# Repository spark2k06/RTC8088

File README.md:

# RTC8088
Real Time Clock for your PC XT. Very low profile, simple and open hardware.

## Hardware Documentation

### Schematic and PCB Layout

[Schematic - Version 3.0](KiCad/RTC8088-Schematic-3.0.pdf)

[PCB Layout - Version 3.0](KiCad/RTC8088-Board-3.0.pdf)

### Swiches and Jumpers

#### SW1 - RTC I/O address select

I/O Address  | SW1.1 | SW 1.2 | SW 1.3
------------ | ----- | ------ | ------
0x70         | OFF   | OFF    | OFF
0x240        | ON    | OFF    | OFF
0x2A0        | OFF   | ON     | OFF
0x2C0        | ON    | ON     | OFF
0x340        | OFF   | OFF    | ON
0x3A0        | ON    | OFF    | ON
0x3C0        | OFF   | ON     | ON
Reserved     | ON    | ON     | ON

* Note 1: The table above gives the addresses in the supplied SPLD fuse map. The selection can be changed by reprogramming the SPLD
* Note 2: "Reserved" address is set to 0x70 in the supplied SPLD fuse map. It is recommended to use this setting when adding a custom I/O address to the SPLD

#### JP1 - Clear CMOS

Position       | Description
-------------- | -----------------
open (default) | Normal operation
closed         | Clear NVRAM memory

### Bill of Materials

#### Version 3.0

[RTC8088 project on Mouser.com](https://www.mouser.com/ProjectManager/ProjectDetail.aspx?AccessID=2877d21cfa) - View and order all components except of the FDC and the PCB.

[RTC8088 on OSH Park](https://oshpark.com/shared_projects/bAF8uwKL) - View and order the PCB.

Component type     | Reference | Description                                     | Quantity | Possible sources and notes 
------------------ | --------- | ----------------------------------------------- | -------- | --------------------------
PCB                |           | RTC8088 PCB - Version 3.0                       | 1        | Order from your favorite PCB manufacturer using provided Gerber files
Integrated Circuit | U1        | DS12885+ - RTC, 24 pin DIP                      | 1        | Mouser [700-DS12885](https://www.mouser.com/ProductDetail/700-DS12885) or [700-DS12885N](https://www.mouser.com/ProductDetail/700-DS12885N)
Integrated Circuit | U2        | ATF16V8B-15PU - Simple Programmable Logic Device, 20 pin DIP | 1 | Mouser [556-AF16V8B15PU](https://www.mouser.com/ProductDetail/556-AF16V8B15PU) or GAL16V8
Quartz Crystal     | Y1        | 32768 Hz, 6 pF                                  | 1        | Mouser [815-AB26T32768KHZ6B](https://www.mouser.com/ProductDetail/815-AB26T32768KHZ6B), [520-ECS327-6-13-X](https://www.mouser.com/ProductDetail/520-ECS327-6-13-X), or [628-VT200F-6PF20PPM](https://www.mouser.com/ProductDetail/628-VT200F-6PF20PPM)
Battery Holder     | BT1       | CR2032 battery holder                           | 1        | Mouser [122-2620-GR](https://www.mouser.com/ProductDetail/122-2620-GR) or [122-2420-GR](https://www.mouser.com/ProductDetail/122-2420-GR)
Battery            | BT1       | CR2032 battery                                  | 1        | Mouser [81-CR2032](https://www.mouser.com/ProductDetail/81-CR2032), [658-CR2032](https://www.mouser.com/ProductDetail/658-CR2032), or [614-CR2032-200](https://www.mouser.com/ProductDetail/614-CR2032-200)
Capacitor          | C1        | 0.1 uF, 50V, MLCC, 5 mm pitch                   | 1        | Mouser [594-K104K15X7RF53H5](https://www.mouser.com/ProductDetail/594-K104K15X7RF53H5) or [810-FG28X7R1H104KNT6](https://www.mouser.com/ProductDetail/810-FG28X7R1H104KNT6)
Resistor Array     | RN1       | 10 kohm, bussed, 5 pin SIP                      | 1        | Mouser [652-4605X-1LF-10K](https://www.mouser.com/ProductDetail/652-4605X-1LF-10K) or [652-4605X-AP1-103LF](https://www.mouser.com/ProductDetail/652-4605X-AP1-103LF)
DIP Switch         | SW1       | DIP switch, 3 position, SPST                    | 1        | Mouser [774-2103MS](https://www.mouser.com/ProductDetail/774-2103MS)
Pin Header         | JP1       | 2 pin header, 2.54 mm pitch                     | 1        | Mouser [649-68002-102HLF](https://www.mouser.com/ProductDetail/649-68002-102HLF)
Jumper             | JP1       | Shunt, 2 pin, 2.54 mm pitch                     | 1        | Mouser [806-SX1100-B](https://www.mouser.com/ProductDetail/806-SX1100-B)
IC Socket          | U1        | 20 pin DIP, 2.54 mm pitch, 7.62 mm row spacing  | 1        | Mouser [649-DILB20P-223TLF](https://www.mouser.com/ProductDetail/649-DILB20P-223TLF)
IC Socket          | U2        | 24 pin DIP, 2.54 mm pitch, 15.24 mm row spacing | 1        | Mouser [649-DILB24P-223TLF](https://www.mouser.com/ProductDetail/649-DILB24P-223TLF)

## Software

The board is supported by the [8088 BIOS](https://github.com/skiselev/8088_bios) and [GLaTICK BIOS Extension](https://github.com/640-KB/GLaTICK).

## Release Notes

### Changes

* Version 3.0
  * Add I/O address configuration switches
  * Remove IRQ configuration jumpers and IRQ support
* Version 2.0
  * Aitor RTC8088
* Version 1.0
  * Initial version

### Known Issues

* No known issues

### Wishlist

* None so far

## Red Tape

### Licensing

RTC8088 is an open source hardware project. The hardware design itself, including schematic and PCB layout design files are licensed under the strongly-reciprocal variant of [CERN Open Hardware Licence version 2](license-cern_ohl_s_v2.txt). The SPLD code is licensed under [GNU General Public License v3](license-gpl-3.0.txt). Documentation, including this file, is licensed under the [Creative Commons Attribution-ShareAlike 4.0 International License](license-cc-by-sa-4.0.txt).

## More information

### Orignal RTC8088 Project Description
https://hackaday.io/project/168972-rtc-isa-8-bits-pcxt

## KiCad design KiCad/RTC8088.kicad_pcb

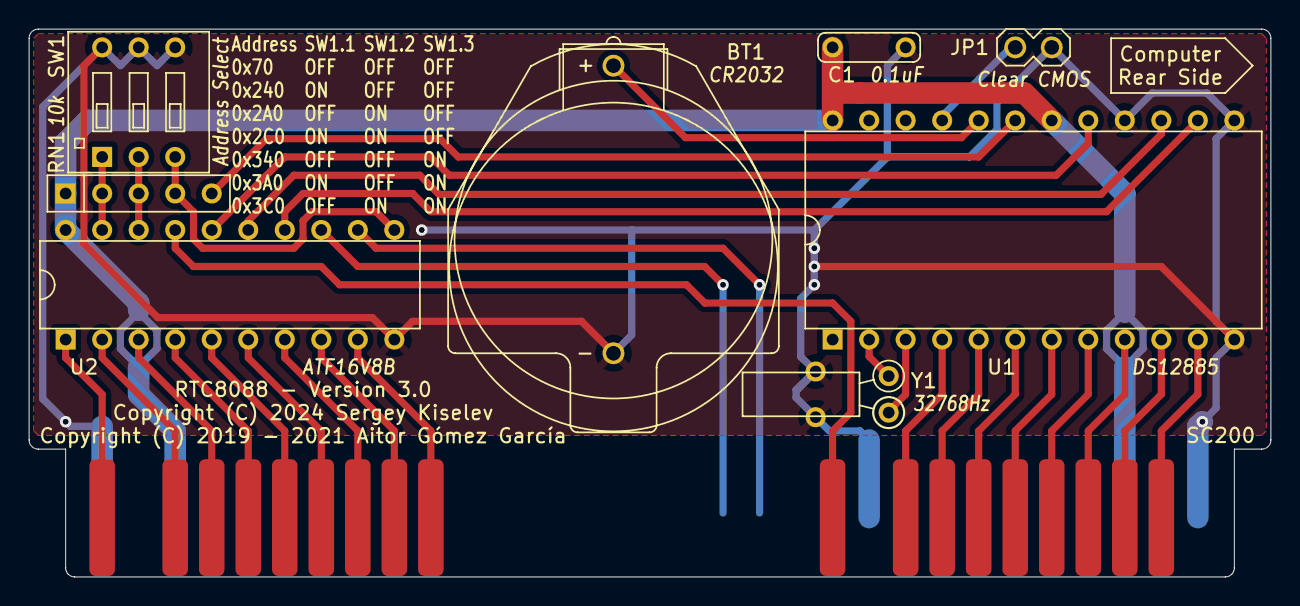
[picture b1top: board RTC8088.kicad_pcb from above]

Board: 2 copper layers, 86.4 x 38.1 mm, 9 parts (0 on the bottom side), 33 nets.

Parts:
BT1: CR2032; Battery_Holder_CR2032_Universal
BUS1: BUSPC_DEV; Conn_Edge_PCB_ISA8
C1: 0.1uF; Cap_Cer_508
JP1: Clear CMOS; Conn_Pin_Header_2x1_2.54mm_NoKey
RN1: 10k; Conn_SIL5
SW1: Address Select; Switch_DIP_3_Positions
U1: DS12885; IC_DIP24_600
U2: ATF16V8B; IC_DIP20_300
Y1: 32768Hz; Crystal_32K_Horiz

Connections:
/A0: BUS1.62 (SA0), U2.1 (I/CLK)
/A2: BUS1.60 (SA2), U2.2 (I1)
/A3: BUS1.59 (SA3), U2.3 (I2)
/A4: BUS1.58 (SA4), U2.4 (I3)
/A5: BUS1.57 (SA5), U2.5 (I4)
/A6: BUS1.56 (SA6), U2.6 (I5)
/A7: BUS1.55 (SA7), U2.7 (I6)
/A8: BUS1.54 (SA8), U2.8 (I7)
/A9: BUS1.53 (SA9), U2.9 (I8)
/AEN: BUS1.42 (AEN), U2.17 (I/O3)
/AS0: RN1.2 (R1), SW1.1, U2.19 (I/O1)
/AS1: RN1.3 (R2), SW1.2, U2.18 (I/O2)
/AS2: RN1.4 (R3), SW1.3, U2.11 (I9/~OE)
/D0: BUS1.40 (SD0), U1.4 (AD0)
/D1: BUS1.39 (SD1), U1.5 (AD1)
/D2: BUS1.38 (SD2), U1.6 (AD2)
/D3: BUS1.37 (SD3), U1.7 (AD3)
/D4: BUS1.36 (SD4), U1.8 (AD4)
/D5: BUS1.35 (SD5), U1.9 (AD5)
/D6: BUS1.34 (SD6), U1.10 (AD6)
/D7: BUS1.33 (SD7), U1.11 (AD7)
/IOR: BUS1.14 (IOR), U2.13 (I/O7)
/IOW: BUS1.13 (IOW), U2.12 (I/O8)
/RTCALE: U1.14 (AS), U2.14 (I/O6)
/RTCRD: U1.17 (DS), U2.16 (I/O4)
/RTCWR: U1.15 (R/~W), U2.15 (I/O5)
/~IRQ: RN1.5 (R4), U1.19 (~IRQ)
GND: BT1.2 (-), BUS1.1 (GND), BUS1.10 (GND), BUS1.31 (GND), C1.2, JP1.2 (B), SW1.4, SW1.5, SW1.6, U1.12 (GND), U1.13 (~CS), U1.16 (GND), U2.10 (GND), Y1.3
unnamed: BT1.1 (+), U1.20 (VBAT)
unnamed: JP1.1 (A), U1.21 (~RCLR)
unnamed: U1.2 (X1), Y1.1
unnamed: U1.3 (X2), Y1.2
VCC: BUS1.3 (VCC), BUS1.29 (VCC), C1.1, RN1.1 (common), U1.18 (~RESET), U1.24 (VCC), U2.20 (VCC)

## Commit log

2021-10-22 I/O port 2C0h and info for other configurations
    JED is added for I / O port 2C0h and the PLD is updated with information for other configurations
2024-04-26 Version 3.0: Implement switches for configuring I/O address
2024-04-26 Add PDF printouts. Add preview of the board
2024-04-26 Fix an error in the layout. Update GitHub repo. Remove unised pads on card edge connector
2024-04-26 Add Bill of Materials
2024-04-26 README: Add Mouser BoM and OshPark PCB links
2024-04-26 README: Add software information, change log, and licensing information
2024-04-26 Add license files
2024-04-26 README: Update licensing section change CPLD to SPLD
2024-04-27 Update silkscreen
2024-04-27 README: Change ON/ON/ON SW1 setting to User Defined to Reserved
2024-04-27 Set OSHW logo attribute to Board Only
2024-04-27 Update silkscreen
    Added logo aitorgomez.net
2024-05-02 README: Fix errors in the BoM
2024-05-08 Fix I/O address 0x2C0 mapping
2024-06-09 Initial implementation of DOS clock driver
2024-06-18 Read and write date and time in one operation; Implement setting day of the week
2024-06-18 Add DSE flag support; Implement date and time validation
2024-11-06 Fix validation problem for 2 digit months
    Credit for this fix goes to @grimjacksl. Fixes issue #11. https://github.com/spark2k06/RTC8088/issues/11

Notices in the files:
KiCad/RTC8088.kicad_pcb:
Copyright (C) 2024 Sergey Kiselev
Copyright (C) 2019 - 2021 Aitor Gómez García
Licensed under CERN-OHL-S:
https://cern-ohl.web.cern.ch
